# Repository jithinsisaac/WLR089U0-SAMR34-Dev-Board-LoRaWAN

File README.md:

### WLR089U0-SAMR34-Dev-Board-LoRaWAN
Development board for Microchip's WLR089U0 LoRaWAN module consisting of the SAMR34 SiP IC 

### PCB Information:
1.  SAMR34 based SiP
2.  Inbuilt u.Fl connector, so no need to worry about RF tuning and impedance matching for PCB tracks
3.  Sleep current of ~2.4uA in Standby mode!
4.  Powered from the USB port
5.  Microchip MCP1700 3.3V LDO
6.  Inbuilt CH340E USB-UART converter. No need for any extra adapter. Serial comm works directly via the USB. CH340E does not require external crystals.
7.  SWD programming via the Cortex debug pin

### Firmware for the board
1.  Use Microchip Studio for firmware programming
2.  Install/Update Microchip ASF 3.48
3.  Open a New Example Project, search for SAMR34
4.  Use 'LoRaWAN Mote Application - SAMR34 Xplained Pro' project
5.  Be sure to choose MLS 1_0_P_4 from ASF version 3.48 (requires LoRaWAN core 1.0.2)
6.  Newer version of MLS 1_0_P_5 requires LoRaWAN core 1.0.4, which may not be compatible with many networks.

### Snapshots:
1. PCB Front

2. PCB Back

3. Finished product 

### Credits
Atul Kumar  (Third Year student, AY2020-2021)  
Jithin Saji Isaac (Assistant Professor, Dept. of EXTC)  
Don Bosco Institute of Technology, Mumbai  
Feb 2021

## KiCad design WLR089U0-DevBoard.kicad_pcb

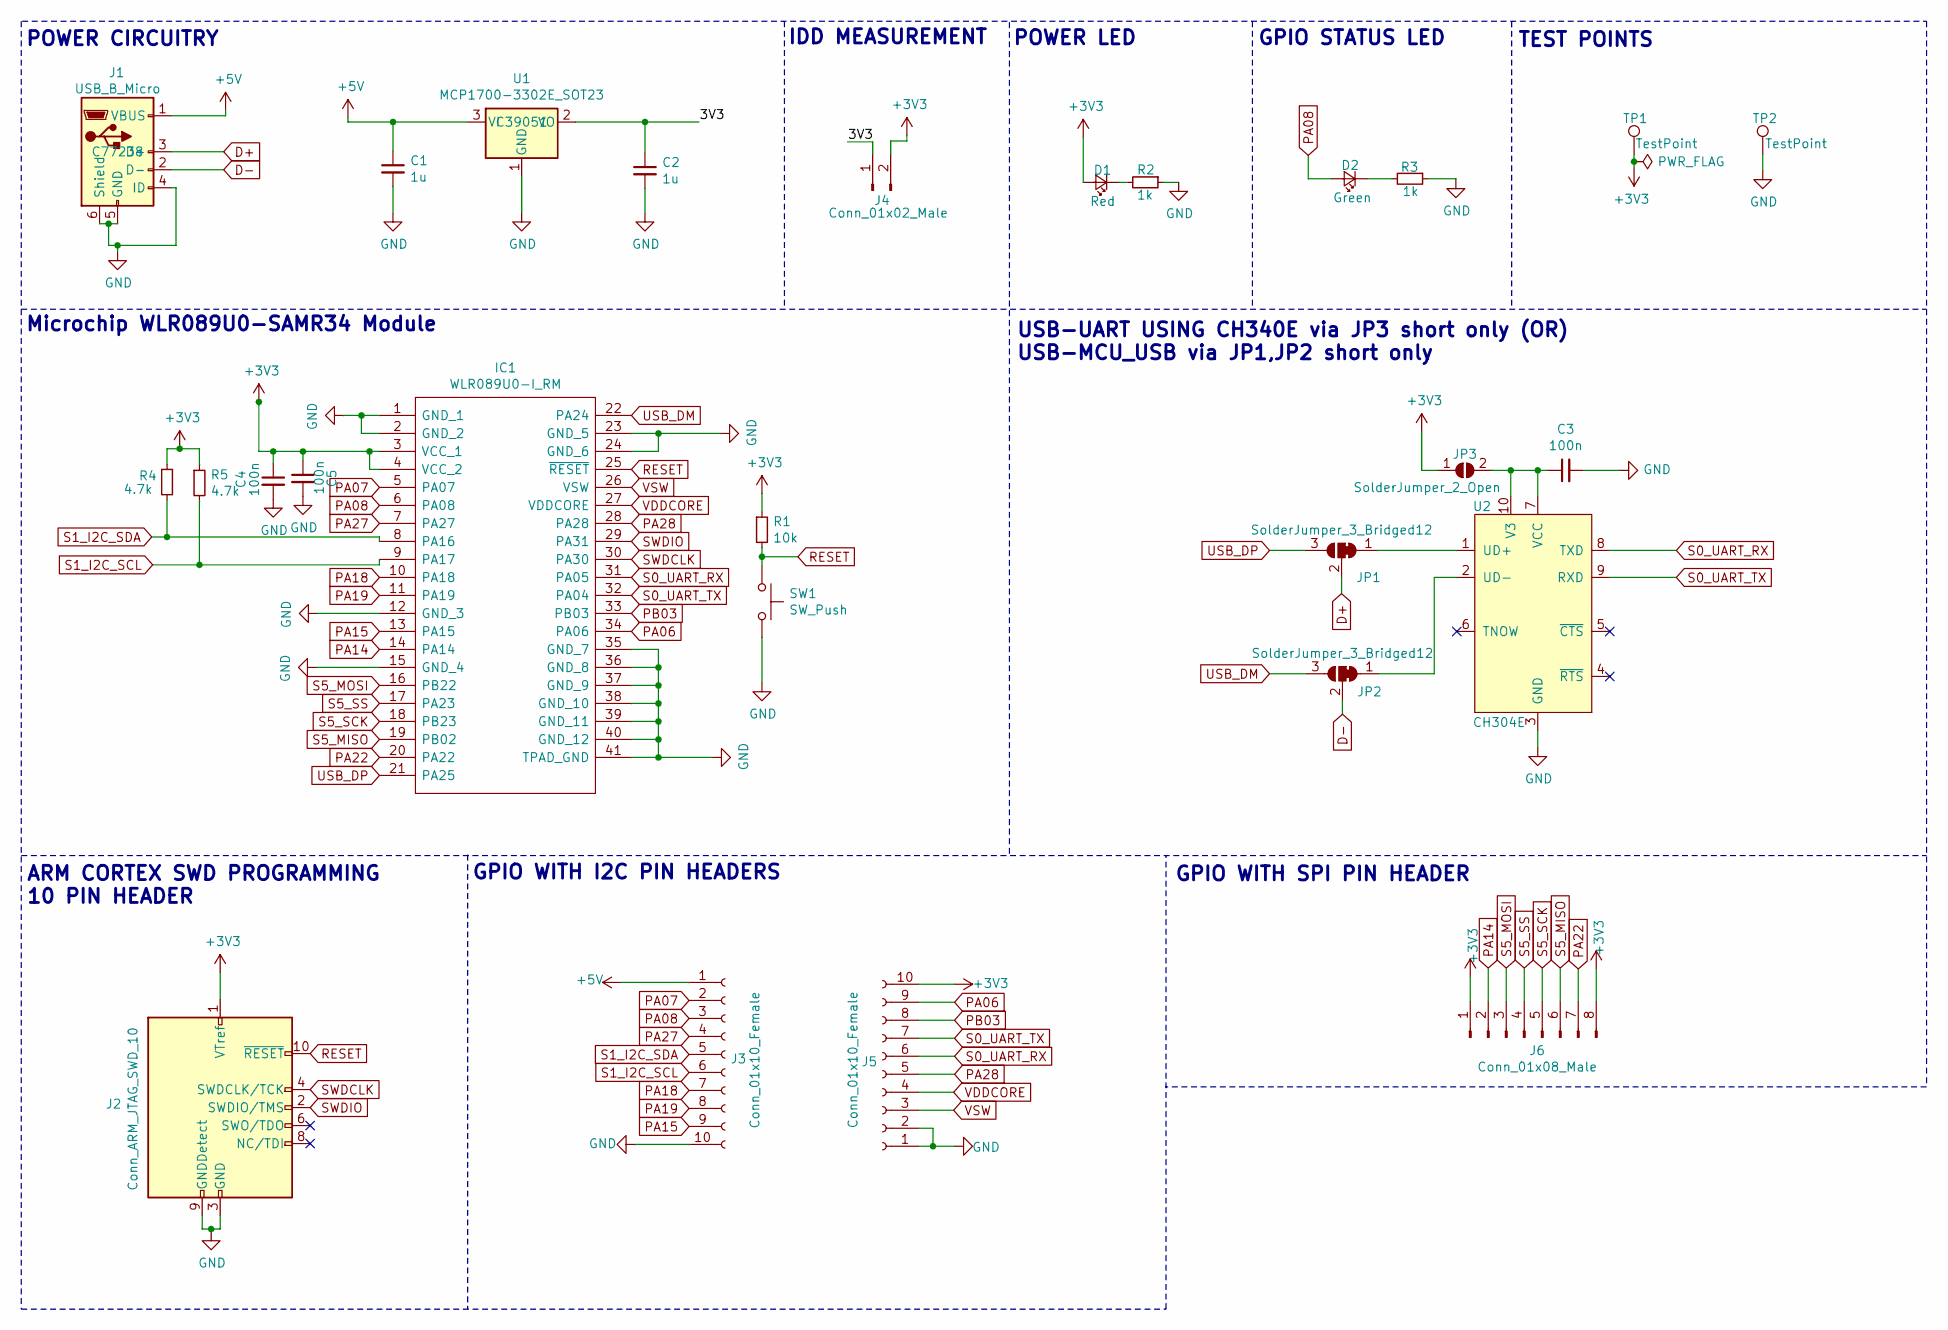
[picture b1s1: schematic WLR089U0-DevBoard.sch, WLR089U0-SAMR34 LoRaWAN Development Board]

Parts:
C1, C2: 1u; C_1206_3216Metric_Pad1.33x1.80mm_HandSolder; Manufacturer_Part_Number 1206B105K250CT; LCSC C412632
C3, C4, C5: 100n; C_1206_3216Metric_Pad1.33x1.80mm_HandSolder; Manufacturer_Part_Number 1206B104K500CT; LCSC C692631
D1: Red; LED_0805_2012Metric_Pad1.15x1.40mm_HandSolder; Manufacturer_Part_Number RD-LED-0805; LCSC C84260
D2: Green; LED_0805_2012Metric_Pad1.15x1.40mm_HandSolder; Manufacturer_Part_Number RD-LED-0805; LCSC C84260
IC1: WLR089U0-I_RM; WLR089U0IRM; Mouser Part Number 579-WLR089U0-I/RM
J1: USB_B_Micro; USB_Micro-AB_Molex_47590-0001; LCSC C77238
J2: Conn_ARM_JTAG_SWD_10; PinHeader_2x05_P1.27mm_Vertical; LCSC C124387
J3, J5: Conn_01x10_Female; PinHeader_1x10_P2.54mm_Vertical; LCSC C57369
J4: Conn_01x02_Male; PinHeader_1x02_P2.54mm_Vertical; LCSC C124375
J6: Conn_01x08_Male; PinHeader_1x08_P2.54mm_Vertical; LCSC C124381
JP1, JP2: SolderJumper_3_Bridged12; SolderJumper-3_P1.3mm_Bridged12_RoundedPad1.0x1.5mm_NumberL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
JP3: SolderJumper_2_Open; SolderJumper-2_P1.3mm_Open_RoundedPad1.0x1.5mm
R1: 10k; R_1206_3216Metric_Pad1.42x1.75mm_HandSolder; LCSC C17902
R2, R3: 1k; R_1206_3216Metric_Pad1.42x1.75mm_HandSolder; LCSC C1469
R4, R5: 4.7k; R_1206_3216Metric_Pad1.42x1.75mm_HandSolder; LCSC C104821
SW1: SW_Push; Tactile Switch 3x4x2mm; LCSC C455280
TP1, TP2: TestPoint; MountingHole_2.2mm_M2_DIN965_Pad_TopBottom
U1: MCP1700-3302E_SOT23; SOT-23; LCSC C39051
U2: CH304E; MSOP-10_3x3mm_P0.5mm; LCSC C99652

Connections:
+3V3: C4.1, C5.1, D1.2 (A), IC1.3 (VCC_1), IC1.4 (VCC_2), J2.1 (VTref), J4.2, J5.10, J6.1, J6.8, JP3.1 (A), R1.1, R4.1, R5.1, TP1.1
+5V: C1.1, J1.1 (VBUS), J3.1, U1.3 (VI)
/3V3: C2.1, J4.1, U1.2 (VO)
D+: J1.3 (D+), JP1.2 (C)
D-: J1.2 (D-), JP2.2 (C)
GND: C1.2, C2.2, C3.2, C4.2, C5.2, IC1.1 (GND_1), IC1.2 (GND_2), IC1.12 (GND_3), IC1.15 (GND_4), IC1.23 (GND_5), IC1.24 (GND_6), IC1.35 (GND_7), IC1.36 (GND_8), IC1.37 (GND_9), IC1.38 (GND_10), IC1.39 (GND_11), IC1.40 (GND_12), IC1.41 (TPAD_GND), J1.4 (ID), J1.5 (GND), J1.6 (Shield), J2.3 (GND), J2.5 (GND), J2.9 (GNDDetect), J3.10, J5.1, J5.2, R2.1, R3.1, SW1.2, TP2.1, U1.1 (GND), U2.3 (GND)
unnamed: C3.1, JP3.2 (B), U2.7 (VCC), U2.10 (V3)
unnamed: D1.1 (K), R2.2
unnamed: D2.1 (K), R3.2
unnamed: JP1.1 (A), U2.1 (UD+)
unnamed: JP2.1 (A), U2.2 (UD-)
PA06: IC1.34 (PA06), J5.9
PA07: IC1.5 (PA07), J3.2
PA08: D2.2 (A), IC1.6 (PA08), J3.3
PA14: IC1.14 (PA14), J6.2
PA15: IC1.13 (PA15), J3.9
PA18: IC1.10 (PA18), J3.7
PA19: IC1.11 (PA19), J3.8
PA22: IC1.20 (PA22), J6.7
PA27: IC1.7 (PA27), J3.4
PA28: IC1.28 (PA28), J5.5
PB03: IC1.33 (PB03), J5.8
RESET: IC1.25 (~RESET), J2.10 (~RESET~), R1.2, SW1.1
S0_UART_RX: IC1.31 (PA05), J5.6, U2.8 (TXD)
S0_UART_TX: IC1.32 (PA04), J5.7, U2.9 (RXD)
S1_I2C_SCL: IC1.9 (PA17), J3.6, R5.2
S1_I2C_SDA: IC1.8 (PA16), J3.5, R4.2
S5_MISO: IC1.19 (PB02), J6.6
S5_MOSI: IC1.16 (PB22), J6.3
S5_SCK: IC1.18 (PB23), J6.5
S5_SS: IC1.17 (PA23), J6.4
SWDCLK: IC1.30 (PA30), J2.4 (SWDCLK/TCK)
SWDIO: IC1.29 (PA31), J2.2 (SWDIO/TMS)
USB_DM: IC1.22 (PA24), JP2.3 (B)
USB_DP: IC1.21 (PA25), JP1.3 (B)
VDDCORE: IC1.27 (VDDCORE), J5.4
VSW: IC1.26 (VSW), J5.3

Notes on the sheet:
ARM CORTEX SWD PROGRAMMING 10 PIN HEADER
Microchip WLR089U0-SAMR34 Module
POWER CIRCUITRY
POWER LED
GPIO STATUS LED
USB-UART USING CH340E via JP3 short only (OR) USB-MCU_USB via JP1,JP2 short only
GPIO WITH I2C PIN HEADERS
GPIO WITH SPI PIN HEADER
IDD MEASUREMENT
TEST POINTS

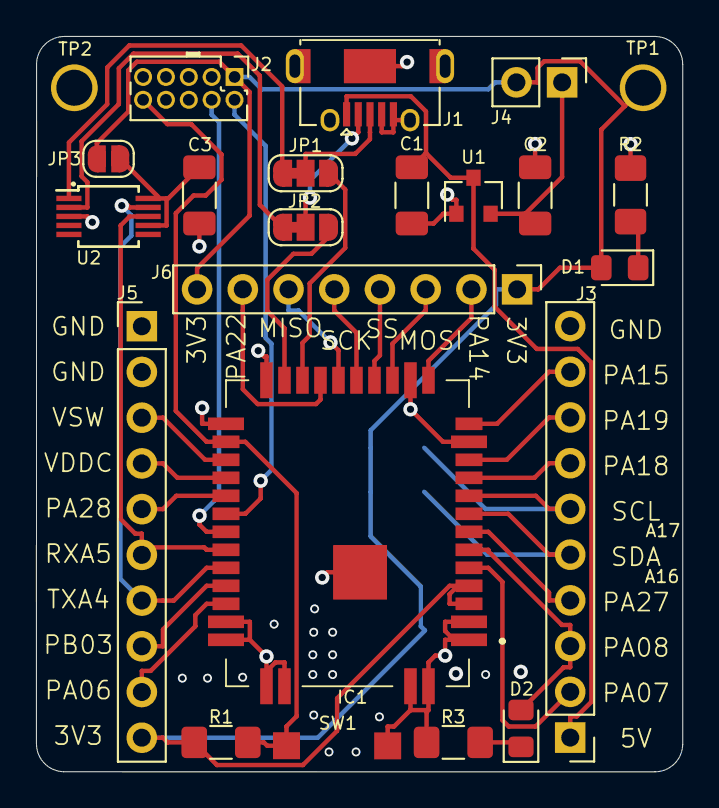
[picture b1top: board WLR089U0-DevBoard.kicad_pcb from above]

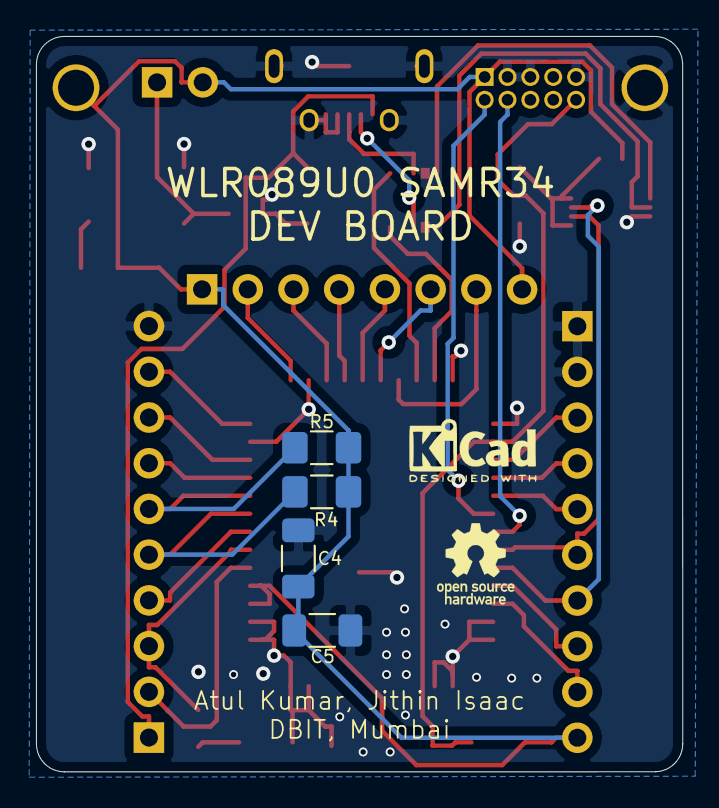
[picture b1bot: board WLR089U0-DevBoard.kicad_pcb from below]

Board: 2 copper layers, 35.9 x 40.9 mm, 28 parts (5 on the bottom side), 37 nets.

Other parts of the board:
KiCad: LOGO; KiCad-Logo2_8X4mm_SilkScreen

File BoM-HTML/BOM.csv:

Designator,Quantity,Value, Manufacturer_Part_NumberC1 C2 ,2,1u,1206B105K250CTC3 C4 C5 ,3,100n,1206B104K500CTD1 ,1,Red,RD-LED-0805D2 ,1,Green,RD-LED-0805IC1 ,1,WLR089U0-I_RM,WLR089U0-I/RMJ1 ,1,USB_B_Micro,DNPJ2 ,1,Conn_ARM_JTAG_SWD_10,DNPJ3 J5 ,2,Conn_01x10_Female,DNPJ4 ,1,Conn_01x02_Male,DNPJ6 ,1,Conn_01x08_Male,DNPJP1 JP2 ,2,SolderJumper_3_Bridged12,DNPJP3 ,1,SolderJumper_2_Open,DNPR1 ,1,10k,DNPR2 R3 ,2,1k,DNPR4 R5 ,2,4.7k,DNPSW1 ,1,SW_Push,DNPTP1 TP2 ,2,TestPoint,DNPU1 ,1,MCP1700-3302E_SOT23,DNPU2 ,1,CH304E,DNP

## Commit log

2021-02-03 Added README.md
2021-02-03 Atul Kumars initial KiCad schematic
2021-02-04 Renamed Files
2021-02-04 edited schematic
2021-02-04 Edited power symbols, ch340e needs to be made
2021-02-04 Power supply done and ch304e remaining
2021-02-04 pins changed and ch304e symbol done
2021-02-04 pins done and symbol ch304e
2021-02-04 blue box and final version done
2021-02-04 Beautified schematic layout, ERC pending
2021-02-04 final schematic
2021-02-05 Schematic done
2021-02-05 Schematic done. reworked drc on test pts
2021-02-05 edited date
2021-02-05 done final editing
2021-02-05 Edited pin placements in schematic
2021-02-08 Added datasheets folder
2021-02-08 PCB Schematic complete
2021-02-08 footprint assignment done
2021-02-08 final footprint assignment
2021-02-09 Updated footprint assignment
2021-02-09 Updated footprint assignment & attached datasheet of switch
2021-02-10 pcb making started
2021-02-10 pcb editing
2021-02-10 removed 5v test point, edited layout edge,microusb edge
2021-02-10 placement of ic2 done
2021-02-10 updated pin header to 8 pin, updated layout
2021-02-10 final pcb layout routing pending
2021-02-11 rearranged layout a bit
2021-02-11 pcb layer remaing
2021-02-11 green layer for gnd
2021-02-11 routing remaining
2021-02-11 routing done
2021-02-11 reduced footprint ref size in silk screen
2021-02-12 labeling done
2021-02-13 editing
2021-02-13 coupling cap placement pending
2021-02-14 Changed orientation, rearranged symbols
2021-02-15 Increased board & SS size, completed layout,routing done. final inspection remains
2021-02-17 Gerber generated
2021-02-17 Edited test pads to remove MAR error, updated Gerber. Will send to fab if asked
2021-03-02 Added HTML BoM
2021-03-02 Updated bom, chnged 100k to 10k for reset circuit
2021-03-03 new gerber
2021-03-07 Added pics folder
2021-06-30 Deleted extra gerber
